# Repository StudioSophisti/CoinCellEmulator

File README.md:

# Coin Cell Emulator

Tired of wasting Coin Cell batteries? With this CR2032 Coin Cell emulator you have an infintely charged battery, connected using USB mini. At Studio Sophisti (http://www.studiosophisti.nl/) we use this PCB intensively in order to reduce our battery consumption.

This product consists out of 2 PCB's that are stacked. If you produce them at 1.6mm thickness, they match exactly the CR2032 size.

### Partlist

- 2 1uF capacitor: Farnell 2496916
- 1 LP3985IM5-3.0 LDO: Farnell 1469153
- 1 MOLEX 67503-1020 Mini USB: Farnell 1125348

### PCB Preview

Generated with GerberTools from ThisIsNotRocketScience (https://github.com/ThisIsNotRocketScience/GerberTools), thanks Stijn!

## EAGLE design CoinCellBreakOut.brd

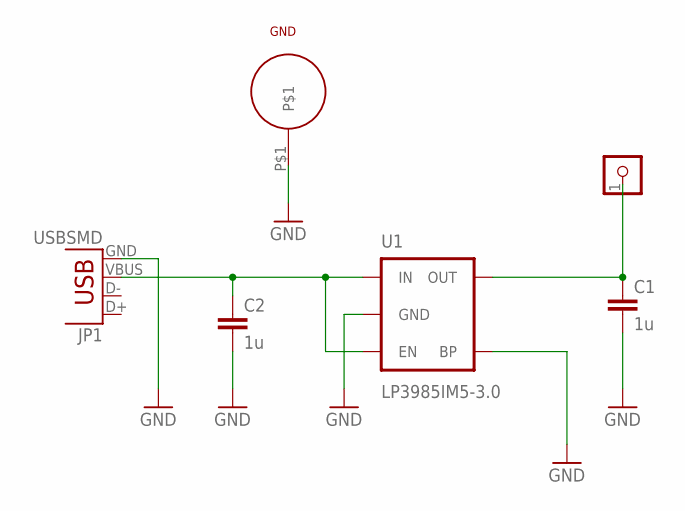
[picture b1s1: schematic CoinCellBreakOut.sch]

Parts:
3V: CON_HEADER_1X01-PTH_10_17; M1X2_10_17
C1, C2: 1u; 0603-CAP
GND: COIN_CELL_CONTACT
JP1: USBSMD; USB-MINIB
U1: LP3985IM5-3.0; SOT23-5

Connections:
GND: C1.2, C2.2, GND.P$1, JP1.GND, U1.2 (GND), U1.4 (BP)
unnamed: C2.1, JP1.VBUS, U1.1 (IN), U1.3 (EN)
unnamed: 3V.1, C1.1, U1.5 (OUT)

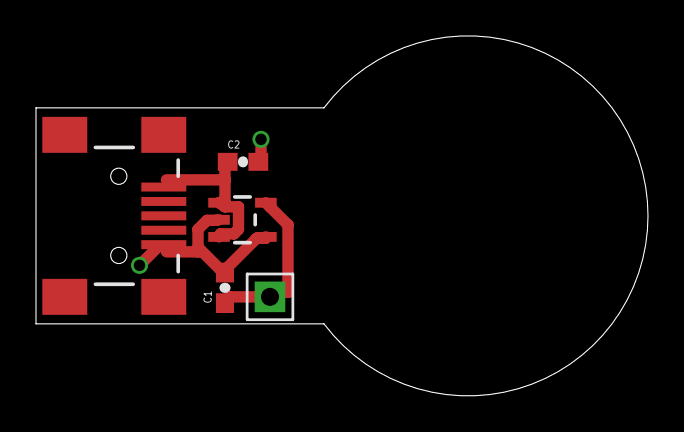
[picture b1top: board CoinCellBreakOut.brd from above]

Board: 2 copper layers, 34.0 x 20.0 mm, 6 parts (1 on the bottom side), 3 nets.

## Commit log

2016-12-23 added eagle files
2016-12-23 fixed tracks near usb connector

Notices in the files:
parts and their libraries:
SparkFun-Connectors: Licensing: Creative Commons ShareAlike 4.0 International - https://creativecommons.org/licenses/by-sa/4.0
